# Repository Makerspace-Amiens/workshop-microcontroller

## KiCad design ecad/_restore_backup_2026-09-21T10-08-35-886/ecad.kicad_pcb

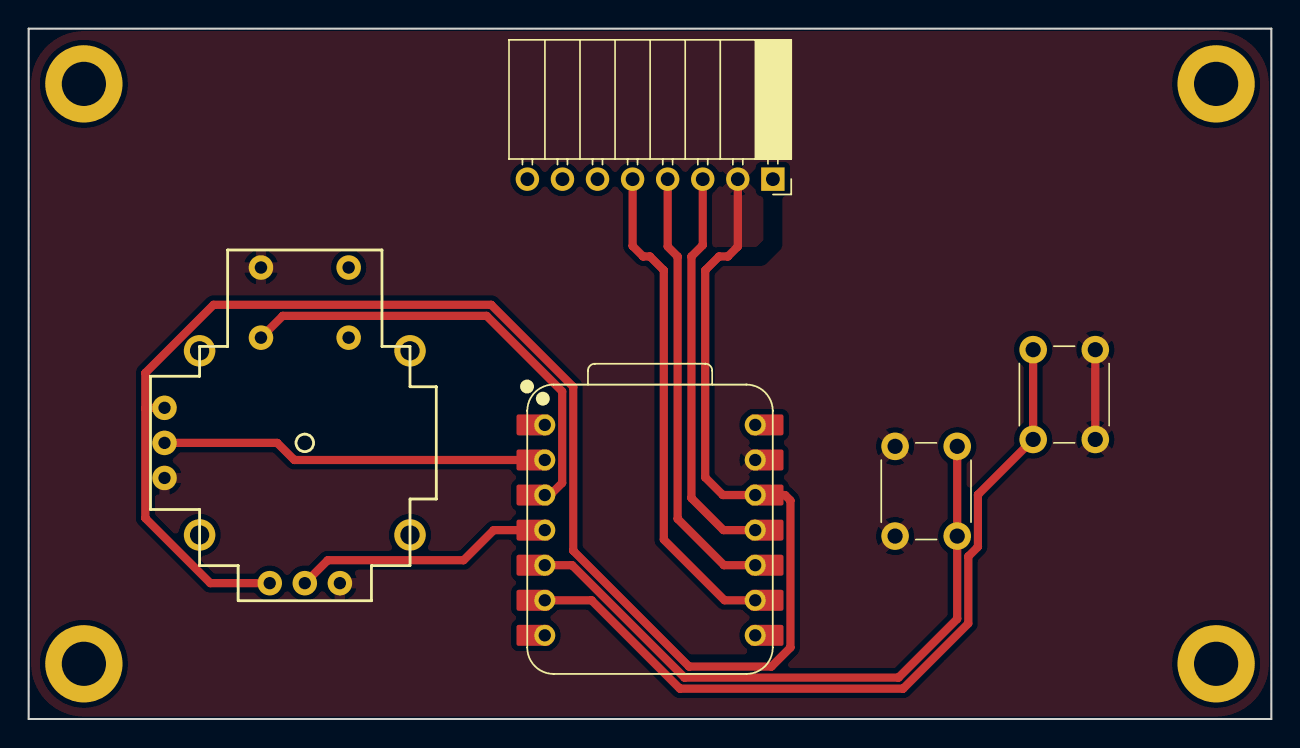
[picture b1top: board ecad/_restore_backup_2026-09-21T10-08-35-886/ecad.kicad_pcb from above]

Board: 2 copper layers, 90.0 x 50.0 mm, 9 parts (0 on the bottom side), 10 nets.

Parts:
H1, H2, H3, H4: MountingHole; MountingHole_3.2mm_M3_DIN965_Pad
J2: Display; PinSocket_1x08_P2.54mm_Horizontal
SW1, SW2: SW_Push; SW_PUSH_6mm
SW5: Joystick; Joystick_PTH
U1: XIAO-ESP32-S3-SMD; xiao-esp32-s3-dip

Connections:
+3.3V: J2.2, SW5.VCC, U1.12 (3V3_OUT)
/MISO: J2.4, U1.10 (D9)
/MOSI: J2.3, U1.11 (D10)
/SCK: J2.5, U1.9 (D8)
GND: J2.1, SW1.2, SW2.2, SW5.GND, U1.13 (GND)
unnamed: SW5.Vertical, U1.2 (D1)
unnamed: SW5.Select, U1.3 (D2)
unnamed: SW5.Horizontal, U1.4 (D3)
unnamed: SW1.1, U1.5 (D4)
unnamed: SW2.1, U1.6 (D5)

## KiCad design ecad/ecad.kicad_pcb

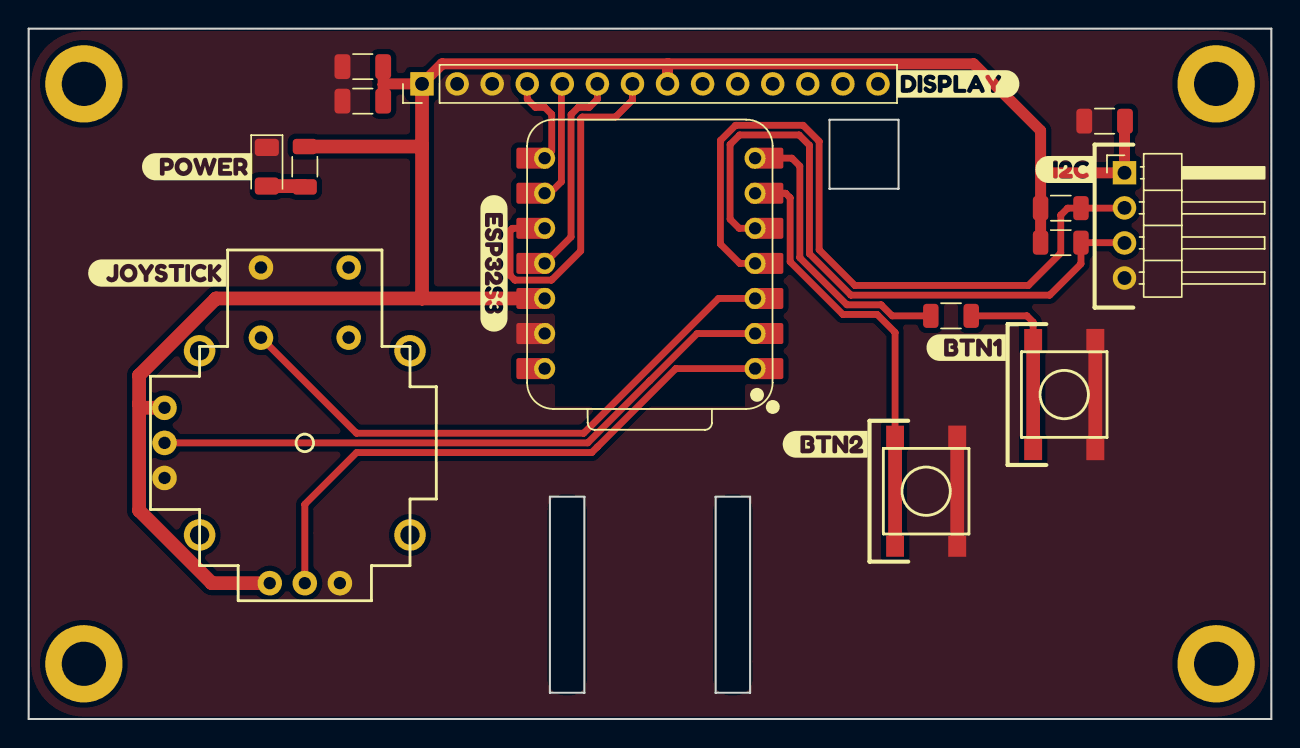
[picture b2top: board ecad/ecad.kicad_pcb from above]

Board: 2 copper layers, 90.0 x 50.0 mm, 25 parts (0 on the bottom side), 15 nets.

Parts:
C2, C3: 0.1u; C_1206_3216Metric
C4: 10u; C_1206_3216Metric
D1: RED; LED_1206_3216Metric
H1, H2, H3, H4: MountingHole; MountingHole_3.2mm_M3_DIN965_Pad
J1: Display; PinHeader_1x14_P2.54mm_Vertical
J3: I2C; PinHeader_1x04_P2.54mm_Horizontal
R1, R4: 1k; R_1206_3216Metric
R2, R3: 4.7k; R_1206_3216Metric
SW1, SW2: SW_Push; Push_SMD_6.2x6.2mm
SW5: Joystick; Joystick_PTH
U1: XIAO-ESP32-S3-SMD; xiao-esp32-s3-dip
kibuzzard-6AB538A8: G***; kibuzzard-6AB538A8
kibuzzard-6AB5389F: G***; kibuzzard-6AB5389F
kibuzzard-6AB53746: G***; kibuzzard-6AB53746
kibuzzard-6AB53801: G***; kibuzzard-6AB53801
kibuzzard-6AB53942: G***; kibuzzard-6AB53942
kibuzzard-6AC64CEE: G***; kibuzzard-6AC64CEE
kibuzzard-6AC64D3E: G***; kibuzzard-6AC64D3E

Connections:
+3.3V: C2.1, C3.1, C4.1, J1.1, J1.8, J3.1, R1.1, R2.1, R3.1, SW5.VCC, U1.12 (3V3_OUT)
/DC: J1.5, U1.9 (D8)
/MOSI: J1.6, U1.11 (D10)
/RESET: J1.4, U1.8 (D7)
/SCK: J1.7, U1.10 (D9)
/SCL: J3.3, R2.2, U1.5 (D4)
/SDA: J3.2, R3.2, U1.4 (D3)
GND: C2.2, C3.2, C4.2, D1.1 (K), J1.2, J1.3, J3.4, SW1.2, SW2.2, SW5.GND, U1.13 (GND)
unnamed: D1.2 (A), R1.2
unnamed: R4.2, SW2.1
unnamed: SW5.Horizontal, U1.1 (D0)
unnamed: SW5.Vertical, U1.2 (D1)
unnamed: SW5.Select, U1.3 (D2)
unnamed: SW1.1, U1.6 (D5)
unnamed: R4.1, U1.7 (D6)
